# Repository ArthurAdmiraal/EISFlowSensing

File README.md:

# Solid state flow sensing using Electrical Impedance Spectroscopy
This repository contains all files for the solid state flow sensing using EIS project, which is documented on hackaday.io, click [here](https://hackaday.io/project/12543-solid-state-flow-sensing-using-eis) to go there.

## License
You can use everything here under a[Creative Commons Attribution-ShareAlike 4.0 International](https://creativecommons.org/licenses/by-sa/4.0/) license.

## Repository structure
Inside the documentation folder, you'll find the source files for images used in the documentation of the project on hackaday.io, along with the rendered versions. The source images are either vector files, or images to large to be uploaded to hackaday.io. You can also find software examples for tutorials placed on hackaday.io there.

The design folder contains CAD files and CAM files needed for replicating the project. The electrical folder contains the KiCad projects for both the electrode and signal generator PCB, along with the gerbers to get them fabricated at [OSH Park](https://oshpark.com/). The mechanical folder contains some OpenScad files for 3D-printed parts, along with STLs for the files that take a long time to render.

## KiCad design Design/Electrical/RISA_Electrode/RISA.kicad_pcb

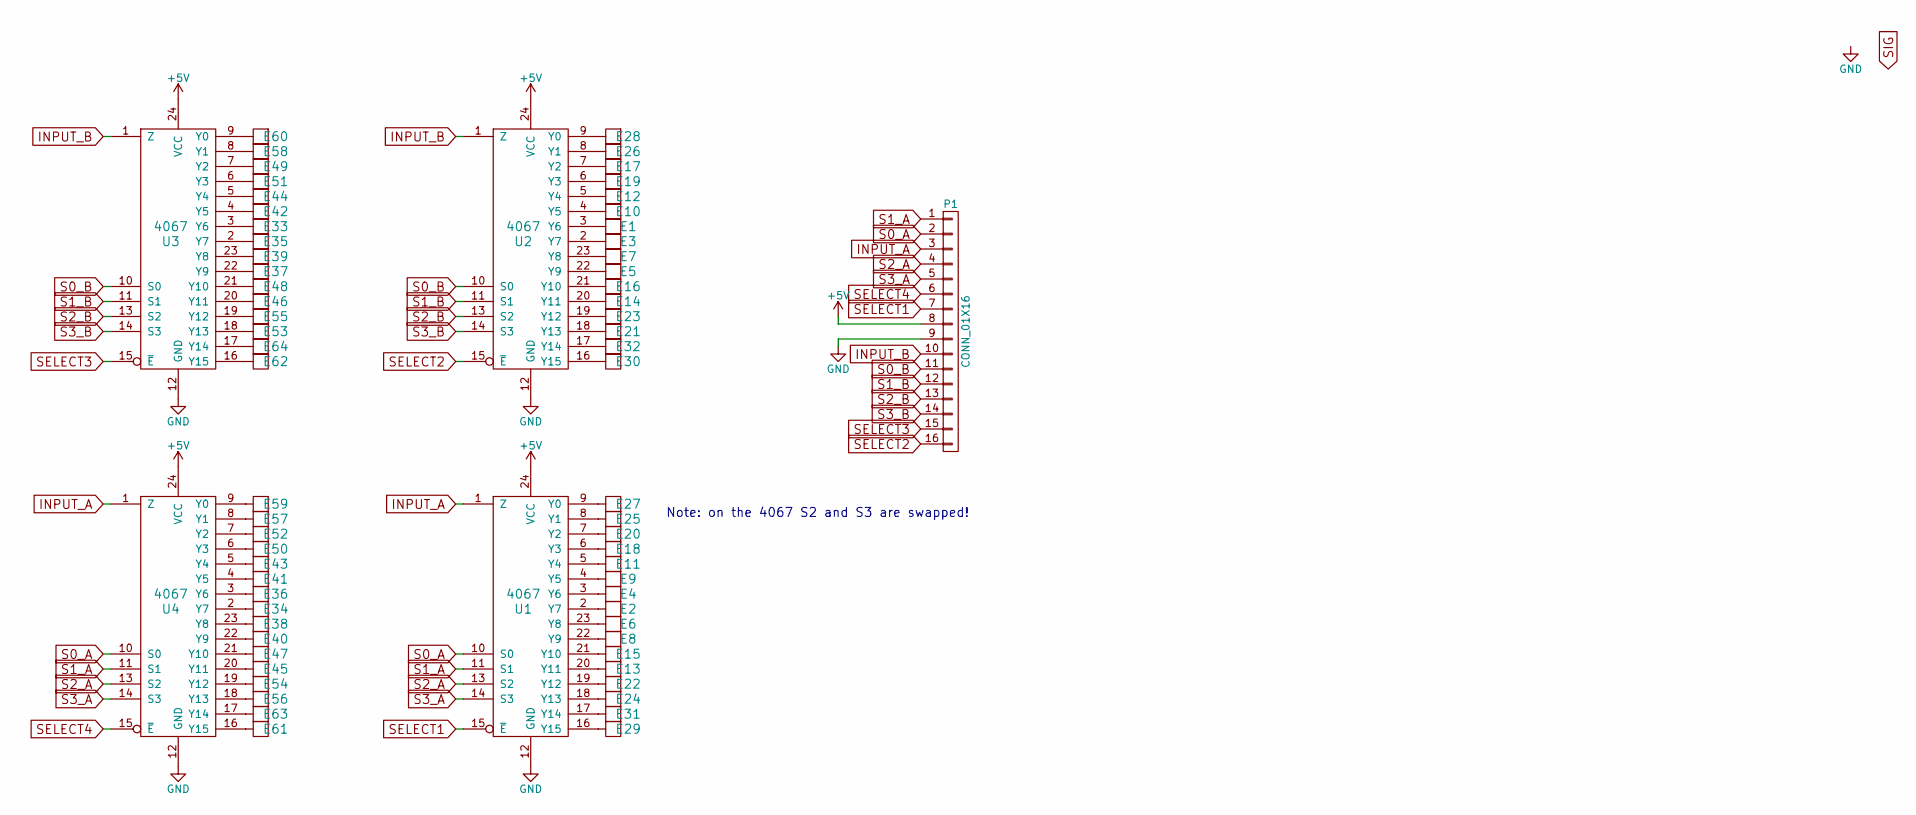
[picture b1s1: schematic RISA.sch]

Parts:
E1, E2, E3, E4, E5, E6, E7, E8, E9, E10, E11, E12, E13, E14, E15, E16, E17, E18, E19, E20, E21, E22, E23, E24, E25, E26, E27, E28, E29, E30, E31, E32, E33, E34, E35, E36, E37, E38, E39, E40, E41, E42, E43, E44, E45, E46, E47, E48, E49, E50, E51, E52, E53, E54, E55, E56, E57, E58, E59, E60, E61, E62, E63, E64: Electrode; ElectrodePad
P1: CONN_01X16; SMT_HEADER_1x16
U1, U2, U3, U4: 4067; SOIC-24_7.5x15.4mm_Pitch1.27mm

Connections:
+5V: P1.8, U1.24 (VCC), U2.24 (VCC), U3.24 (VCC), U4.24 (VCC)
GND: P1.9, U1.12 (GND), U2.12 (GND), U3.12 (GND), U4.12 (GND)
INPUT_A: P1.3, U1.1 (Z), U4.1 (Z)
INPUT_B: P1.10, U2.1 (Z), U3.1 (Z)
unnamed: E1.1, U2.3 (Y6)
unnamed: E2.1, U1.2 (Y7)
unnamed: E3.1, U2.2 (Y7)
unnamed: E4.1, U1.3 (Y6)
unnamed: E5.1, U2.22 (Y9)
unnamed: E6.1, U1.23 (Y8)
unnamed: E7.1, U2.23 (Y8)
unnamed: E8.1, U1.22 (Y9)
unnamed: E9.1, U1.4 (Y5)
unnamed: E10.1, U2.4 (Y5)
unnamed: E11.1, U1.5 (Y4)
unnamed: E12.1, U2.5 (Y4)
unnamed: E13.1, U1.20 (Y11)
unnamed: E14.1, U2.20 (Y11)
unnamed: E15.1, U1.21 (Y10)
unnamed: E16.1, U2.21 (Y10)
unnamed: E17.1, U2.7 (Y2)
unnamed: E18.1, U1.6 (Y3)
unnamed: E19.1, U2.6 (Y3)
unnamed: E20.1, U1.7 (Y2)
unnamed: E21.1, U2.18 (Y13)
unnamed: E22.1, U1.19 (Y12)
unnamed: E23.1, U2.19 (Y12)
unnamed: E24.1, U1.18 (Y13)
unnamed: E25.1, U1.8 (Y1)
unnamed: E26.1, U2.8 (Y1)
unnamed: E27.1, U1.9 (Y0)
unnamed: E28.1, U2.9 (Y0)
unnamed: E29.1, U1.16 (Y15)
unnamed: E30.1, U2.16 (Y15)
unnamed: E31.1, U1.17 (Y14)
unnamed: E32.1, U2.17 (Y14)
unnamed: E33.1, U3.3 (Y6)
unnamed: E34.1, U4.2 (Y7)
unnamed: E35.1, U3.2 (Y7)
unnamed: E36.1, U4.3 (Y6)
unnamed: E37.1, U3.22 (Y9)
unnamed: E38.1, U4.23 (Y8)
unnamed: E39.1, U3.23 (Y8)
unnamed: E40.1, U4.22 (Y9)
unnamed: E41.1, U4.4 (Y5)
unnamed: E42.1, U3.4 (Y5)
unnamed: E43.1, U4.5 (Y4)
unnamed: E44.1, U3.5 (Y4)
unnamed: E45.1, U4.20 (Y11)
unnamed: E46.1, U3.20 (Y11)
unnamed: E47.1, U4.21 (Y10)
unnamed: E48.1, U3.21 (Y10)
unnamed: E49.1, U3.7 (Y2)
unnamed: E50.1, U4.6 (Y3)
unnamed: E51.1, U3.6 (Y3)
unnamed: E52.1, U4.7 (Y2)
unnamed: E53.1, U3.18 (Y13)
unnamed: E54.1, U4.19 (Y12)
unnamed: E55.1, U3.19 (Y12)
unnamed: E56.1, U4.18 (Y13)
unnamed: E57.1, U4.8 (Y1)
unnamed: E58.1, U3.8 (Y1)
unnamed: E59.1, U4.9 (Y0)
unnamed: E60.1, U3.9 (Y0)
unnamed: E61.1, U4.16 (Y15)
unnamed: E62.1, U3.16 (Y15)
unnamed: E63.1, U4.17 (Y14)
unnamed: E64.1, U3.17 (Y14)
S0_A: P1.2, U1.10 (S0), U4.10 (S0)
S0_B: P1.11, U2.10 (S0), U3.10 (S0)
S1_A: P1.1, U1.11 (S1), U4.11 (S1)
S1_B: P1.12, U2.11 (S1), U3.11 (S1)
S2_A: P1.4, U1.13 (S2), U4.13 (S2)
S2_B: P1.13, U2.13 (S2), U3.13 (S2)
S3_A: P1.5, U1.14 (S3), U4.14 (S3)
S3_B: P1.14, U2.14 (S3), U3.14 (S3)
SELECT1: P1.7, U1.15 (~E)
SELECT2: P1.16, U2.15 (~E)
SELECT3: P1.15, U3.15 (~E)
SELECT4: P1.6, U4.15 (~E)

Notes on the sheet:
Note: on the 4067 S2 and S3 are swapped!

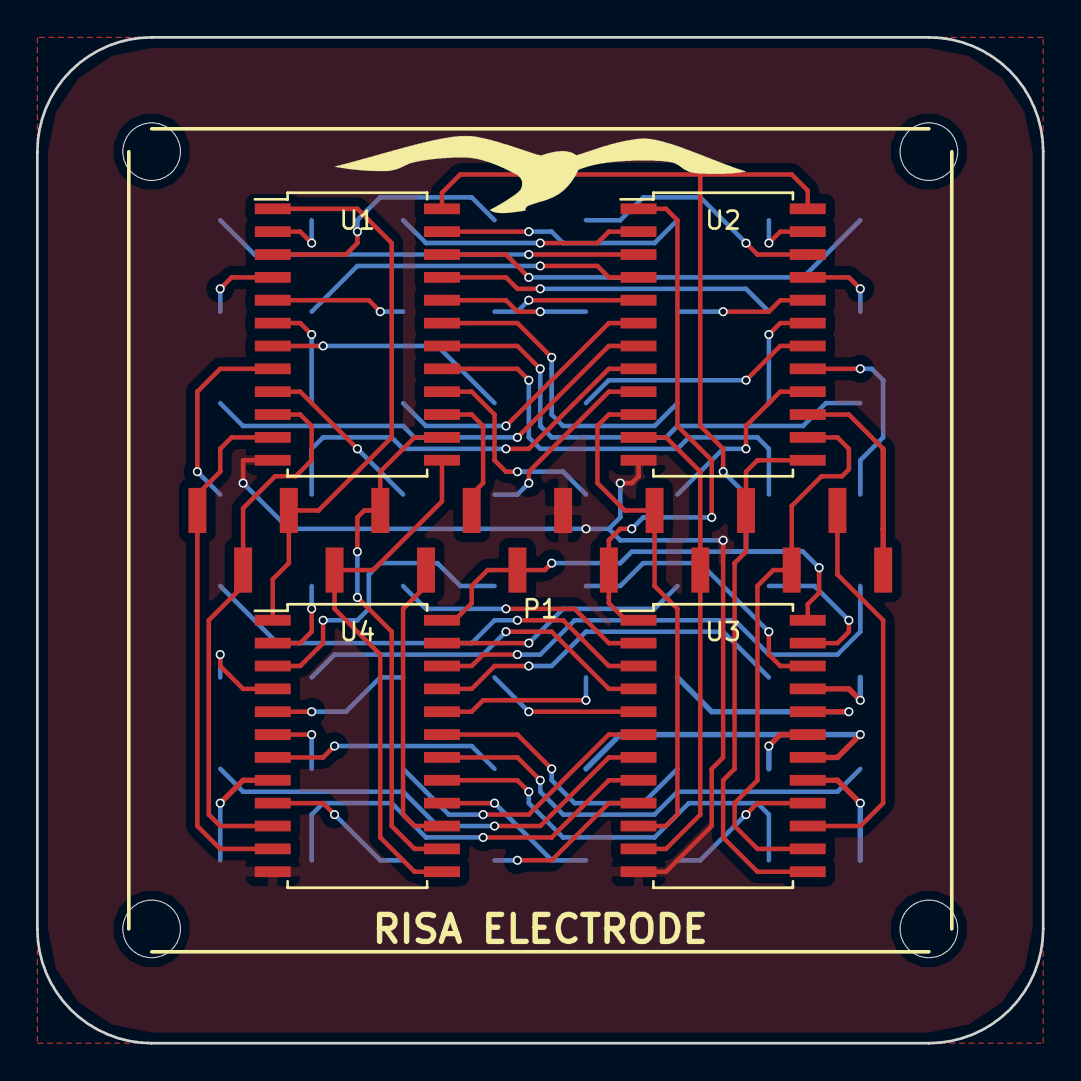
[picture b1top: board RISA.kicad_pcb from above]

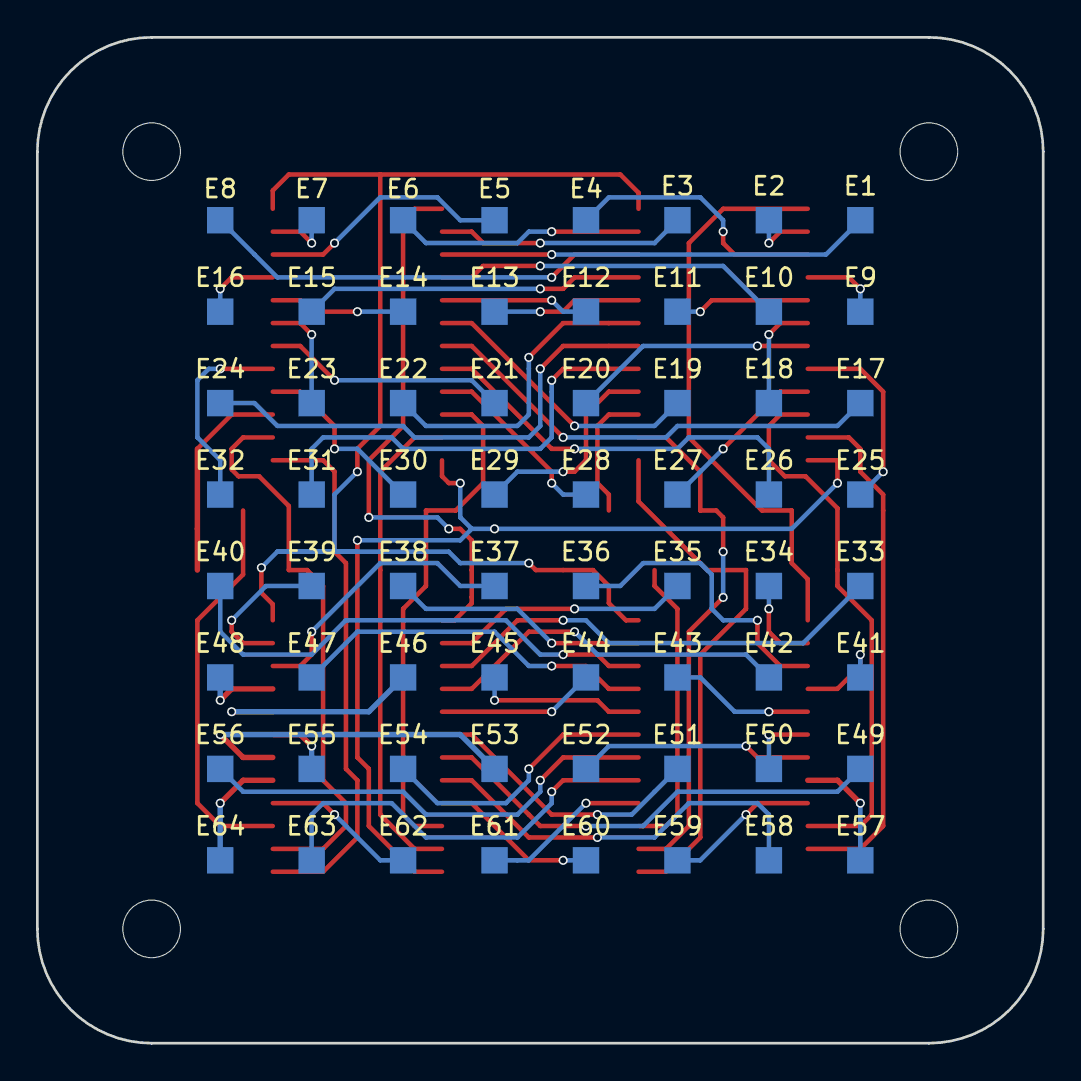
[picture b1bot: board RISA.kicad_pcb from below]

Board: 2 copper layers, 55.9 x 55.9 mm, 69 parts (64 on the bottom side), 80 nets.

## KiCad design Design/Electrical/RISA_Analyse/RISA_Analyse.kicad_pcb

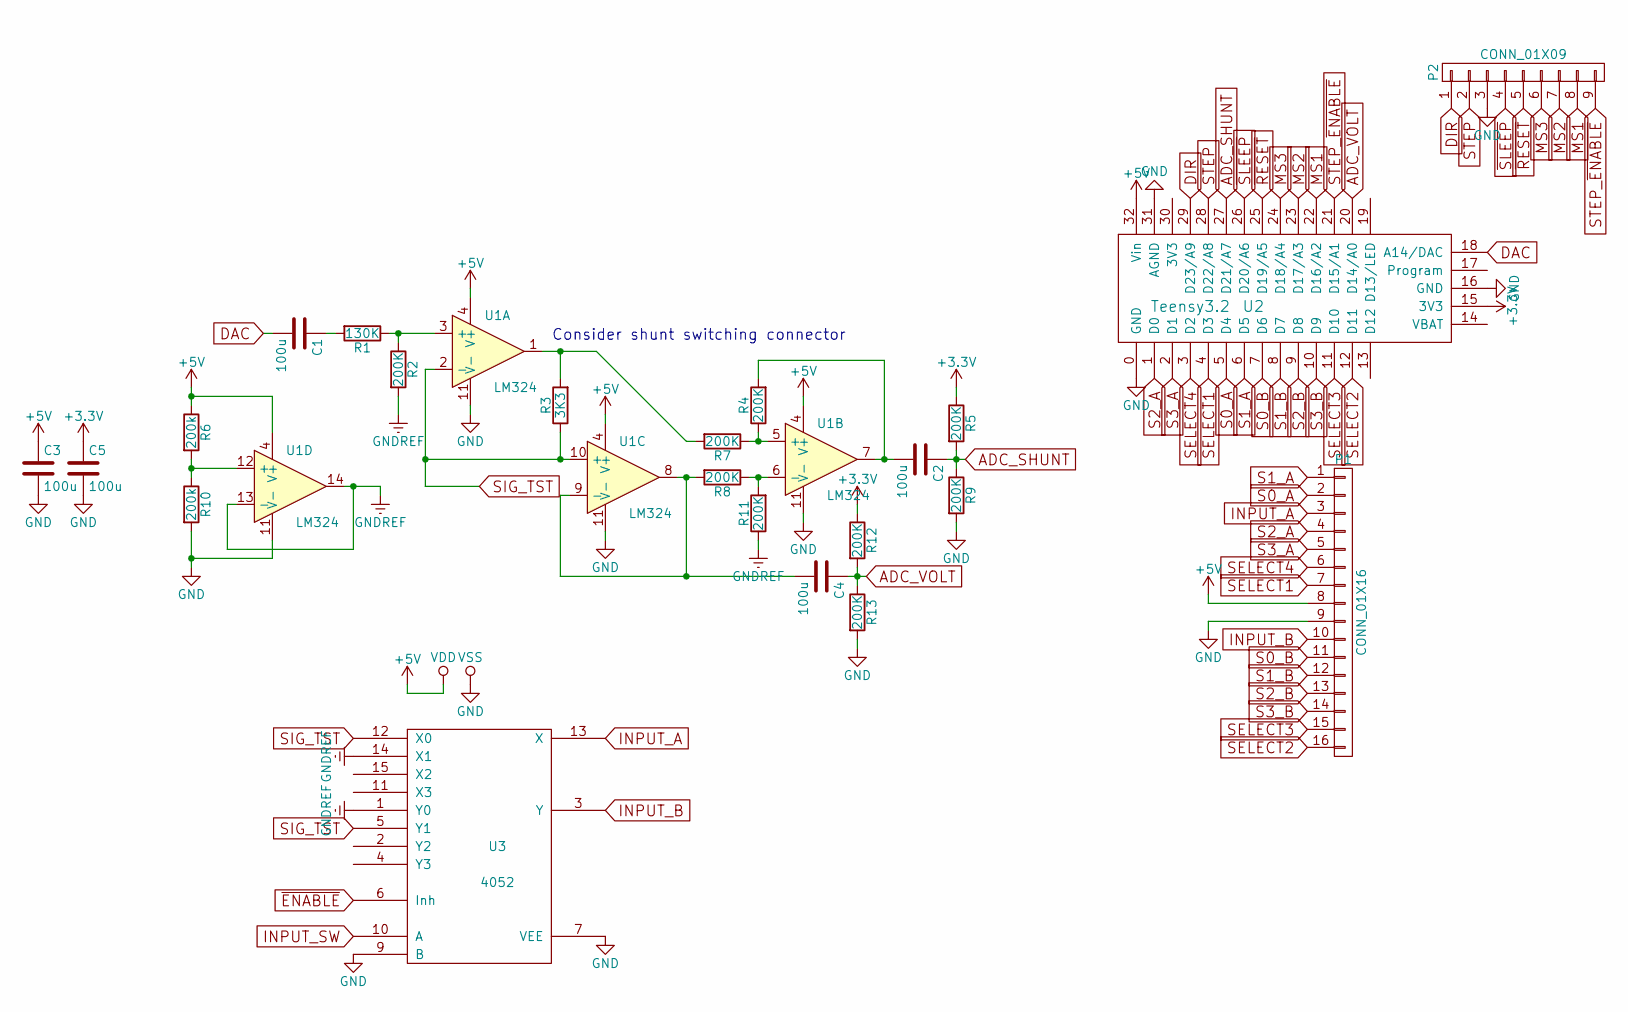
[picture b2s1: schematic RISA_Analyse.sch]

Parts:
C1, C2, C3, C4, C5: 100u; C_Rect_L7_W4.5_P5
P1: CONN_01X16; Pin_Header_Straight_1x16
P2: CONN_01X09; Pin_Header_Straight_1x09
R1: 130K; Resistor_Horizontal_RM7mm
R2, R4, R5, R7, R8, R9, R11, R12, R13: 200K; Resistor_Horizontal_RM7mm
R3: 3K3; Resistor_Horizontal_RM7mm
R6, R10: 200k; Resistor_Horizontal_RM7mm
U1: LM324; DIP-14_W7.62mm
U2: Teensy3.2
U3: 4052; DIP-16_W7.62mm

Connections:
+3V3: C5.1, R5.1, R12.1, U2.15 (3V3)
+5V: C3.1, P1.8, R6.1, U1.4 (V+), U2.32 (Vin), U3.16 (VDD)
ADC_SHUNT: C2.1, R5.2, R9.1, U2.27 (D21/A7)
ADC_VOLT: C4.1, R12.2, R13.1, U2.20 (D14/A0)
DAC: C1.2, U2.18 (A14/DAC)
DIR: P2.1, U2.29 (D23/A9)
GND: C3.2, C5.2, P1.9, P2.3, R9.2, R10.2, R13.2, U1.11 (V-), U2.0 (GND), U2.16 (GND), U2.31 (AGND), U3.7 (VEE), U3.8 (VSS), U3.9 (B)
GNDREF: R2.2, R11.1, U1.13 (-), U1.14, U3.1 (Y0), U3.14 (X1)
INPUT_A: P1.3, U3.13 (X)
INPUT_B: P1.10, U3.3 (Y)
INPUT_SW: U3.10 (A)
MS1: P2.8, U2.22 (D16/A2)
MS2: P2.7, U2.23 (D17/A3)
MS3: P2.6, U2.24 (D18/A4)
unnamed: C1.1, R1.2
unnamed: C2.2, R4.2, U1.7
unnamed: C4.2, R8.2, U1.8, U1.9 (-)
unnamed: R1.1, R2.1, U1.3 (+)
unnamed: R3.2, R7.2, U1.1
unnamed: R4.1, R7.1, U1.5 (+)
unnamed: R6.2, R10.1, U1.12 (+)
unnamed: R8.1, R11.2, U1.6 (-)
S0_A: P1.2, U2.5 (D4)
S0_B: P1.11, U2.7 (D6)
S1_A: P1.1, U2.6 (D5)
S1_B: P1.12, U2.8 (D7)
S2_A: P1.4, U2.1 (D0)
S2_B: P1.13, U2.9 (D8)
S3_A: P1.5, U2.2 (D1)
S3_B: P1.14, U2.10 (D9)
SELECT1: P1.7, U2.4 (D3)
SELECT2: P1.16, U2.12 (D11)
SELECT3: P1.15, U2.11 (D10)
SELECT4: P1.6, U2.3 (D2)
SIG_TST: R3.1, U1.2 (-), U1.10 (+), U3.5 (Y1), U3.12 (X0)
STEP: P2.2, U2.28 (D22/A8)
STEP_~ENABLE: P2.9, U2.21 (D15/A1)
~ENABLE: U3.6 (Inh)
~RESET: P2.5, U2.25 (D19/A5)
~SLEEP: P2.4, U2.26 (D20/A6)

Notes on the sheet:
Consider shunt switching connector

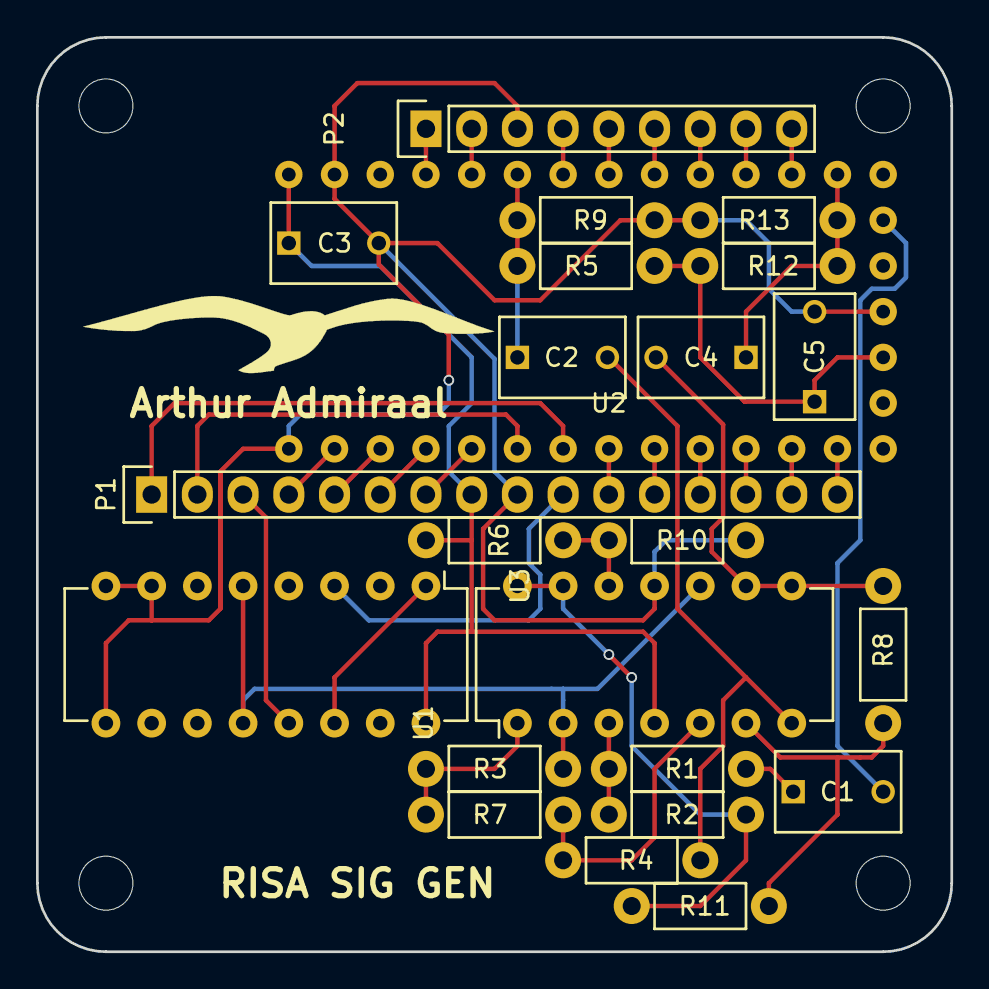
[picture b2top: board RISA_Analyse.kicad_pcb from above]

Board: 2 copper layers, 50.8 x 50.8 mm, 23 parts (0 on the bottom side), 38 nets.

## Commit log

2016-07-07 Adds some new images
2016-07-10 Adds electrical documentation and schematic pdfs
2016-07-10 Adds DAC buffered DMA example
2016-07-10 Adds some images for the project status log
2016-07-10 Adds build instruction images
2016-07-24 Adds more built and documentation images
2016-07-24 Updates mechanical design
2016-07-24 Adds mechanical renders
2016-07-24 Adds case documentation
